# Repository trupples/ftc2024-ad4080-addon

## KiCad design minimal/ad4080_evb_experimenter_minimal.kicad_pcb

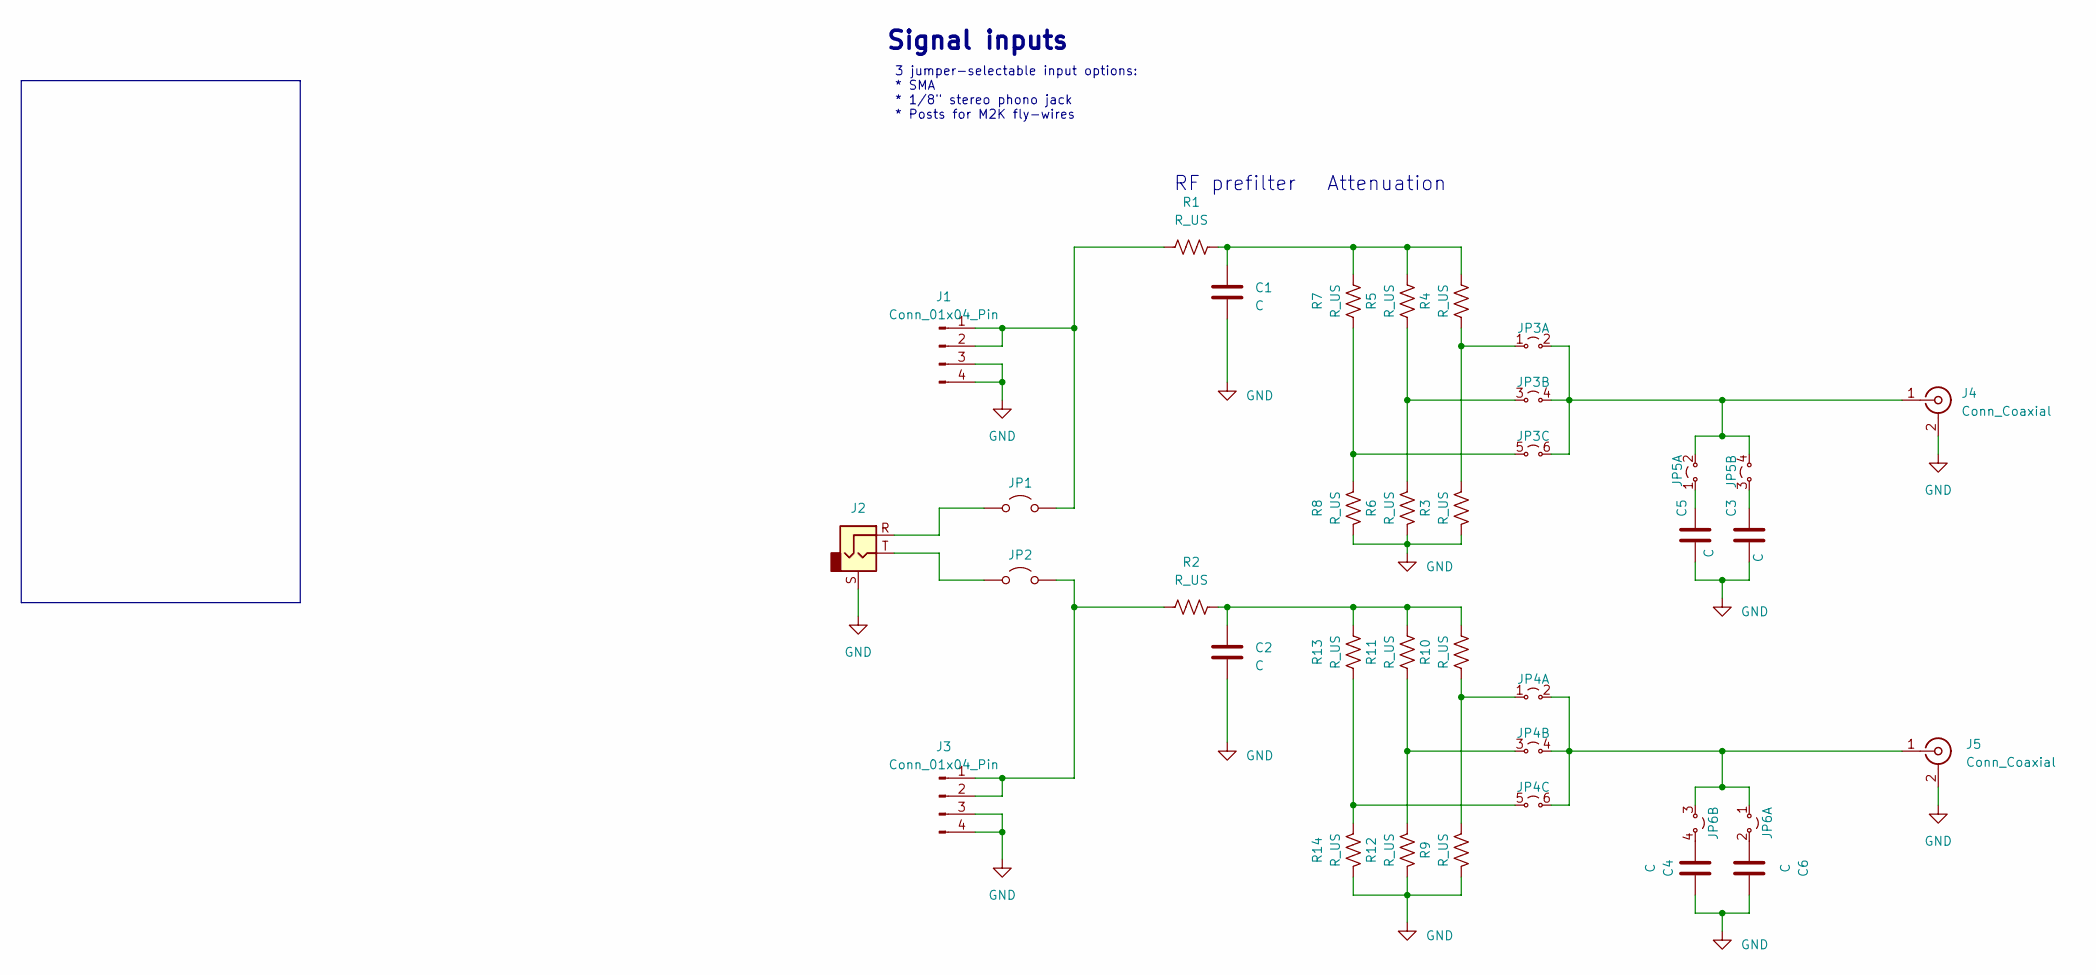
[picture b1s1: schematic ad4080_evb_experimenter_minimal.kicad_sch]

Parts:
C1, C2, C3, C4, C5, C6: C; C_1206_3216Metric_Pad1.33x1.80mm_HandSolder
J1, J3: Conn_01x04_Pin; PinHeader_1x04_P2.54mm_Vertical
J2: AudioJack2_Ground; Jack_3.5mm_CUI_SJ1-3533NG_Horizontal
J4, J5: Conn_Coaxial; SMA_Amphenol_132289_EdgeMount
JP1, JP2: Jumper_2_Open; PinHeader_1x02_P2.54mm_Vertical
JP3, JP4: PinHeader_2x03_P2.54mm_Vertical
JP5, JP6: PinHeader_2x02_P2.54mm_Vertical
R1, R2, R3, R4, R5, R6, R7, R8, R9, R10, R11, R12, R13, R14: R_US; R_1206_3216Metric_Pad1.30x1.75mm_HandSolder

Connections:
GND: C1.2, C2.2, C3.1, C4.2, C5.1, C6.2, J1.3, J1.4, J2.S, J3.3, J3.4, J4.2 (Ext), J5.2 (Ext), R3.2, R6.2, R8.2, R9.2, R12.2, R14.2
unnamed: C1.1, R1.2, R4.2, R5.2, R7.2
unnamed: C2.1, R2.2, R10.2, R11.2, R13.2
unnamed: C3.2, JP5.3
unnamed: C4.1, JP6.4
unnamed: C5.2, JP5.1
unnamed: C6.1, JP6.2
unnamed: J1.1, J1.2, JP1.2 (B), R1.1
unnamed: J3.1, J3.2, JP2.2 (B), R2.1
unnamed: J4.1 (In), JP3.2, JP3.4, JP3.6, JP5.2, JP5.4
unnamed: J5.1 (In), JP4.2, JP4.4, JP4.6, JP6.1, JP6.3
unnamed: J2.R, JP1.1 (A)
unnamed: J2.T, JP2.1 (A)
unnamed: JP3.1, R3.1, R4.1
unnamed: JP3.3, R5.1, R6.1
unnamed: JP3.5, R7.1, R8.1
unnamed: JP4.1, R9.1, R10.1
unnamed: JP4.3, R11.1, R12.1
unnamed: JP4.5, R13.1, R14.1

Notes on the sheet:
RF prefilter
3 jumper-selectable input options: * SMA * 1/8" stereo phono jack * Posts for M2K fly-wires
Signal inputs
Attenuation

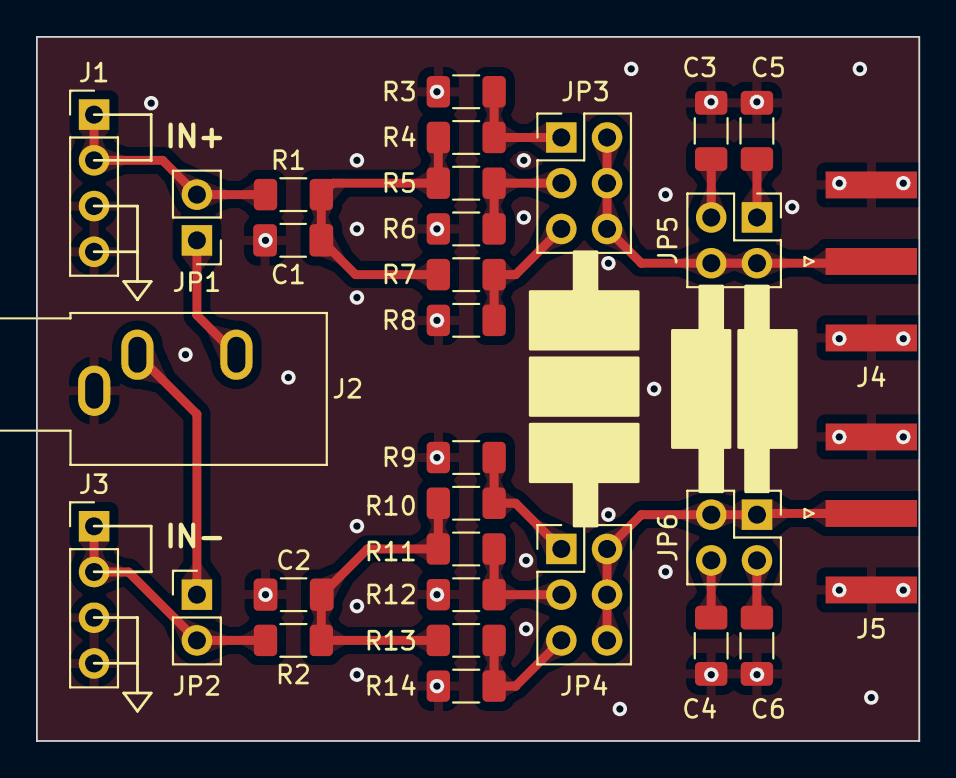
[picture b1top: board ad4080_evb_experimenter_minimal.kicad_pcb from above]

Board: 2 copper layers, 49.0 x 39.1 mm, 31 parts (0 on the bottom side), 19 nets.

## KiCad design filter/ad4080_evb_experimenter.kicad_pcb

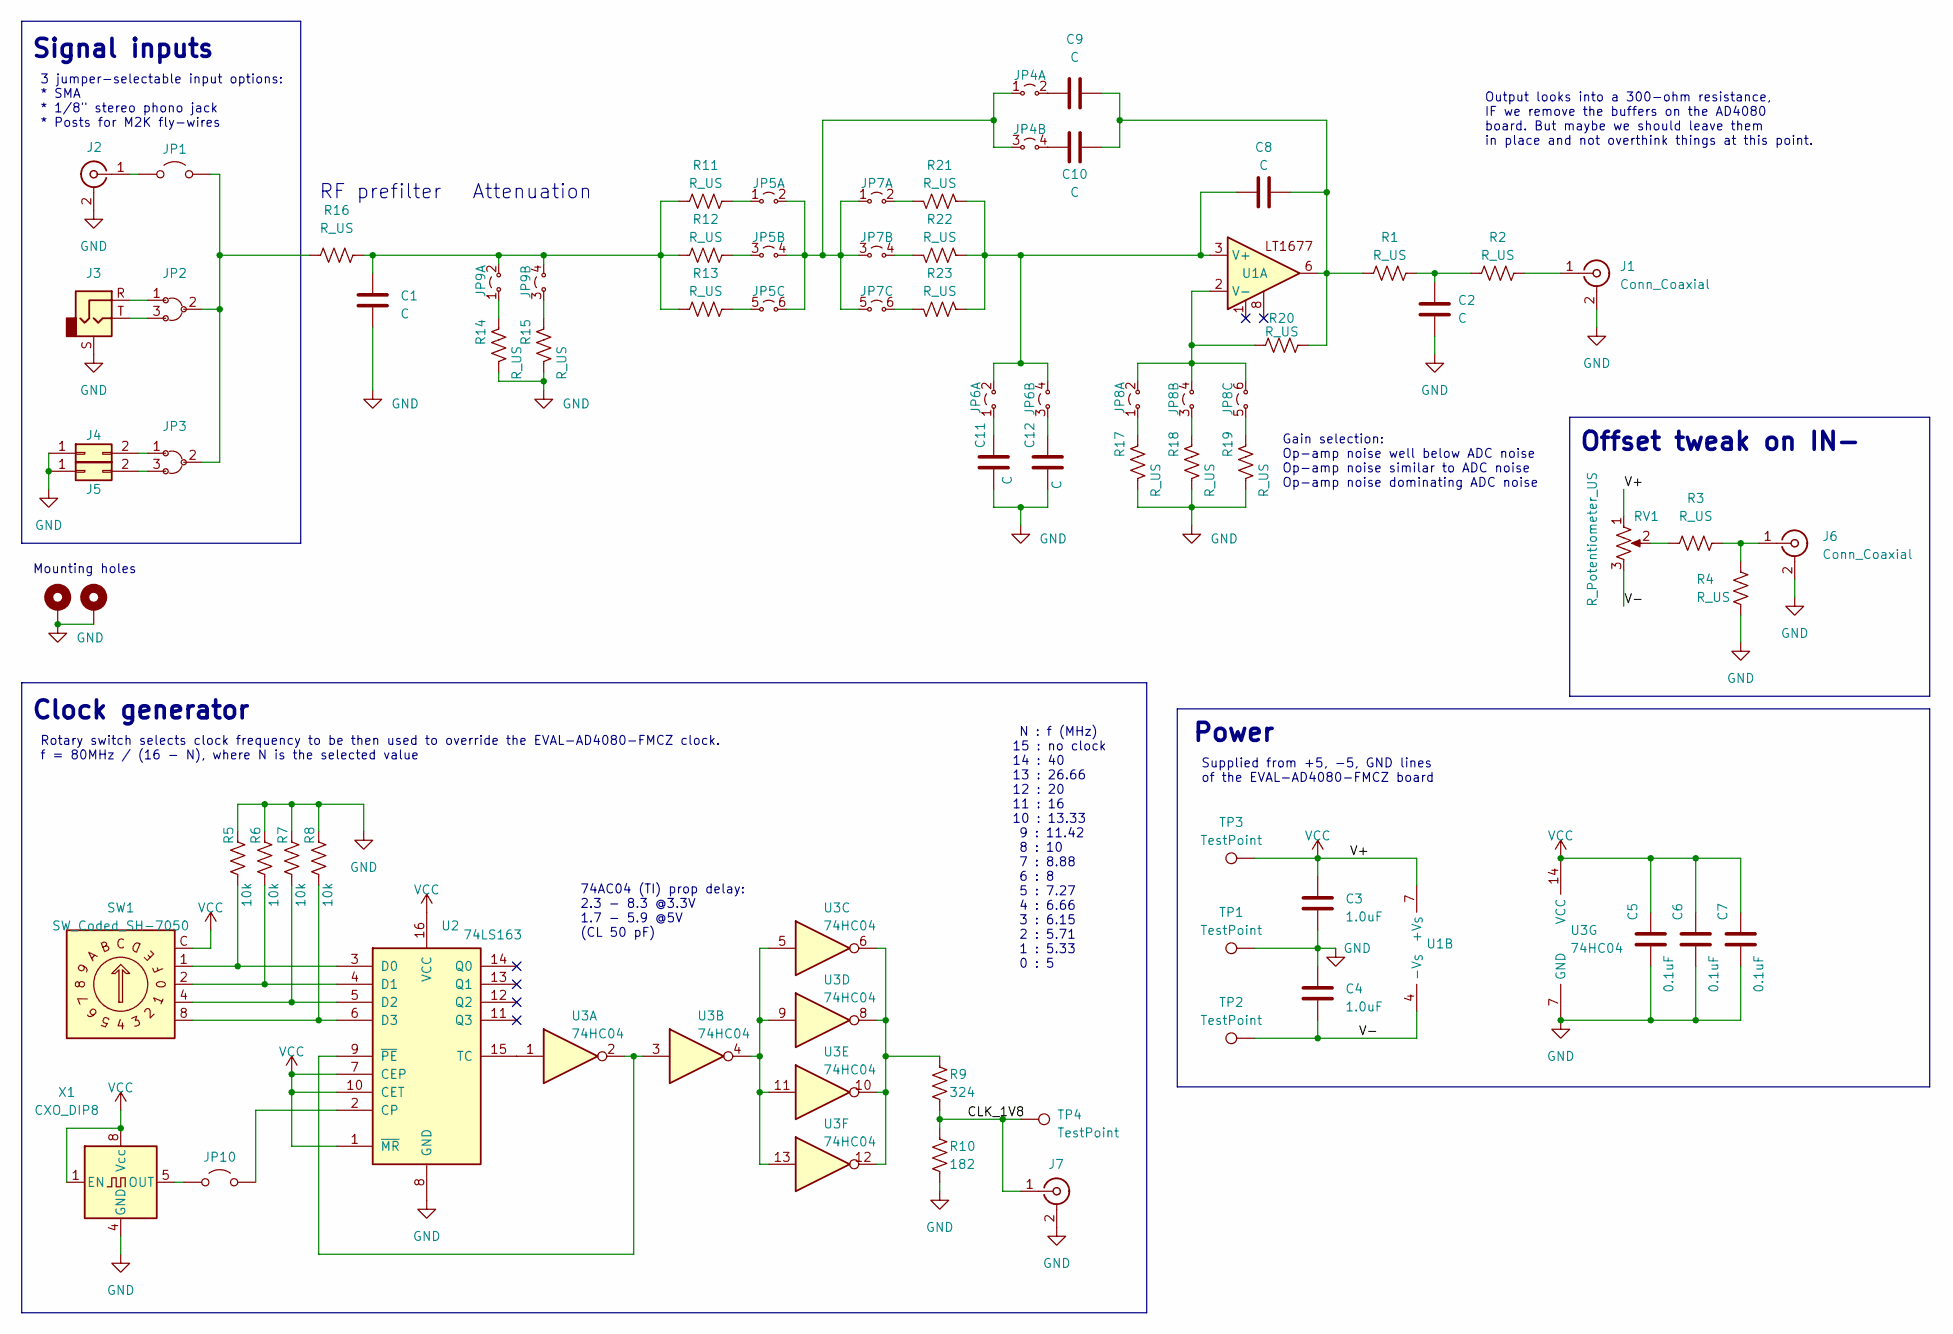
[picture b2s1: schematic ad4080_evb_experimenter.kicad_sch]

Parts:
C1, C2, C8, C9, C10, C11, C12: C; C_Rect_L7.2mm_W2.5mm_P5.00mm_FKS2_FKP2_MKS2_MKP2
C3, C4: 1.0uF; C_Rect_L7.2mm_W2.5mm_P5.00mm_FKS2_FKP2_MKS2_MKP2
C5, C6, C7: 0.1uF; C_Rect_L7.2mm_W2.5mm_P5.00mm_FKS2_FKP2_MKS2_MKP2
H1, H2: MountingHole_Pad; MountingHole_3mm_Pad
J1, J2, J6, J7: Conn_Coaxial; SMA_Amphenol_132289_EdgeMount
J3: AudioJack2_Ground; Jack_3.5mm_CUI_SJ1-3533NG_Horizontal
J4, J5: Conn_02x01; PinHeader_1x02_P2.54mm_Vertical
JP1, JP10: Jumper_2_Open; PinHeader_1x02_P2.54mm_Vertical
JP2, JP3: PinHeader_1x03_P2.54mm_Vertical
JP4, JP6, JP9: PinHeader_2x02_P2.54mm_Vertical
JP5, JP7, JP8: PinHeader_2x03_P2.54mm_Vertical
R1, R2, R3, R4, R11, R12, R13, R14, R15, R16, R17, R18, R19, R20, R21, R22, R23: R_US; R_Axial_DIN0207_L6.3mm_D2.5mm_P10.16mm_Horizontal
R5, R6, R7, R8: 10k; R_Axial_DIN0207_L6.3mm_D2.5mm_P10.16mm_Horizontal
R9: 324; R_Axial_DIN0207_L6.3mm_D2.5mm_P10.16mm_Horizontal
R10: 182; R_Axial_DIN0207_L6.3mm_D2.5mm_P10.16mm_Horizontal
RV1: R_Potentiometer_US; Potentiometer_Bourns_3386F_Vertical
SW1: SW_Coded_SH-7050; FD01KR16P
TP1, TP2, TP3, TP4: TestPoint; TestPoint_Keystone_5005-5009_Compact
U1: DIP-8_W7.62mm
U2: 74LS163; DIP-16_W7.62mm_LongPads
U3: 74HC04; DIP-14_W7.62mm_LongPads
X1: CXO_DIP8; Oscillator_DIP-8

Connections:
/CLK_1V8: J7.1 (In), R9.1, R10.2, TP4.1
/V-: C4.2, RV1.3, TP2.1, U1.4 (-V_{S})
GND: C1.2, C2.2, C3.2, C4.1, C5.2, C6.2, C7.2, C11.1, C12.1, H1.1, H2.1, J1.2 (Ext), J2.2 (Ext), J3.S, J4.1, J5.1, J6.2 (Ext), J7.2 (Ext), R4.1, R5.2, R6.2, R7.2, R8.2, R10.1, R14.1, R15.1, R17.1, R18.1, R19.1, TP1.1, U2.8 (GND), U3.7 (GND), X1.4 (GND)
unnamed: C1.1, JP9.2, JP9.4, R11.1, R12.1, R13.1, R16.2
unnamed: C2.1, R1.2, R2.1
unnamed: C9.1, JP4.2
unnamed: C10.1, JP4.4
unnamed: C8.2, C9.2, C10.2, R1.1, R20.1, U1.6
unnamed: C11.2, JP6.1
unnamed: C12.2, JP6.3
unnamed: J1.1 (In), R2.2
unnamed: J2.1 (In), JP1.1 (A)
unnamed: J3.R, JP2.1
unnamed: J3.T, JP2.3
unnamed: J4.2, JP3.1
unnamed: J5.2, JP3.3
unnamed: J6.1 (In), R3.2, R4.2
unnamed: JP1.2 (B), JP2.2, JP3.2, R16.1
unnamed: JP4.1, JP4.3, JP5.2, JP5.4, JP5.6, JP7.1, JP7.3, JP7.5
unnamed: JP5.1, R11.2
unnamed: JP5.3, R12.2
unnamed: JP5.5, R13.2
unnamed: JP7.2, R21.2
unnamed: JP7.4, R22.2
unnamed: JP7.6, R23.2
unnamed: JP8.1, R17.2
unnamed: JP8.3, R18.2
unnamed: JP8.5, R19.2
unnamed: JP9.1, R14.2
unnamed: JP9.3, R15.2
unnamed: JP10.1 (A), X1.5 (OUT)
unnamed: JP10.2 (B), U2.2 (CP)
unnamed: R3.1, RV1.2
unnamed: R9.2, U3.6, U3.8, U3.10, U3.12
unnamed: C8.1, JP6.2, JP6.4, R21.1, R22.1, R23.1, U1.3 (V+)
unnamed: JP8.2, JP8.4, JP8.6, R20.2, U1.2 (V-)
unnamed: R5.1, SW1.1, U2.3 (D0)
unnamed: R6.1, SW1.2, U2.4 (D1)
unnamed: R7.1, SW1.4, U2.5 (D2)
unnamed: R8.1, SW1.8, U2.6 (D3)
unnamed: U2.15 (TC), U3.1
unnamed: U2.9 (~PE), U3.2, U3.3
unnamed: U3.4, U3.5, U3.9, U3.11, U3.13
VCC: C3.1, C5.1, C6.1, C7.1, RV1.1, SW1.C, TP3.1, U1.7 (+V_{S}), U2.1 (~MR), U2.7 (CEP), U2.10 (CET), U2.16 (VCC), U3.14 (VCC), X1.1 (EN), X1.8 (Vcc)

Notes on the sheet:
Clock generator
RF prefilter
74AC04 (TI) prop delay: 2.3 - 8.3 @3.3V 1.7 - 5.9 @5V (CL 50 pF)
Mounting holes
Supplied from +5, -5, GND lines of the EVAL-AD4080-FMCZ board
N : f (MHz) 15 : no clock 14 : 40 13 : 26.66 12 : 20 11 : 16 10 : 13.33 9 : 11.42 8 : 10 7 : 8.88 6 : 8 5 : 7.27 4 : 6.66 3 : 6.15 2 : 5.71 1 : 5.33 0 : 5
3 jumper-selectable input options: * SMA * 1/8" stereo phono jack * Posts for M2K fly-wires
Output looks into a 300-ohm resistance, IF we remove the buffers on the AD4080 board. But maybe we should leave them in place and not overthink things at this point.
Signal inputs
Offset tweak on IN-
Rotary switch selects clock frequency to be then used to override the EVAL-AD4080-FMCZ clock. f = 80MHz / (16 - N), where N is the selected value
Attenuation
Gain selection: Op-amp noise well below ADC noise Op-amp noise similar to ADC noise Op-amp noise dominating ADC noise
Power

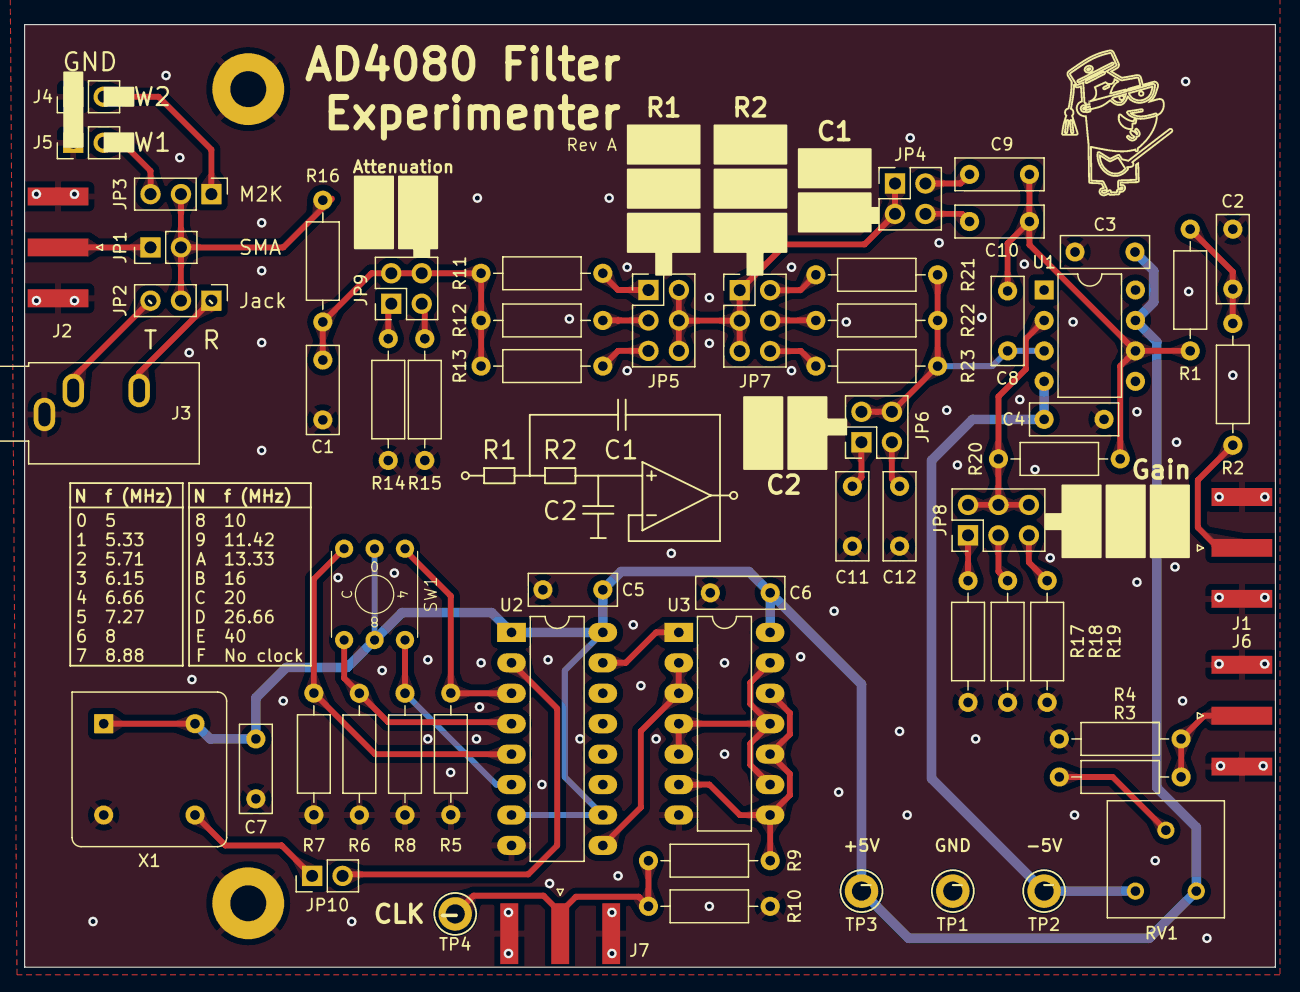
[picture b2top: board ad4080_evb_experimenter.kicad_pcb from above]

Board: 2 copper layers, 104.4 x 78.7 mm, 64 parts (0 on the bottom side), 44 nets.

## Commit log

2024-08-22 Initial draft
2024-08-26 Reduced unused space, fix DRC errors
2024-09-03 Single opamp, decouple digital power, selectable attenuation, routing and silkscreen tweaks
2024-09-03 routing tweaks and more vias
2024-09-03 Shrink opamp neg feedback loop
2024-09-03 Set correct 14mm output SMA spacing
2024-09-03 Fix sallen key silkscreen
2024-09-17 Fix swapped rotary encoder pins 2,8
2024-09-17 Fix flipped opamp inputs
2024-09-17 Change to 2 layers
2024-09-17 Change test points to smaller Keystone Miniature
2024-09-17 Add mounting holes, 3mm
2024-09-17 Generate gerbers
2024-09-24 Add clock output SMA
2024-09-24 Prepare structure for two boards
2024-09-24 First minimal board draft
2024-09-24 Adjust vias, routes, silkscreen
